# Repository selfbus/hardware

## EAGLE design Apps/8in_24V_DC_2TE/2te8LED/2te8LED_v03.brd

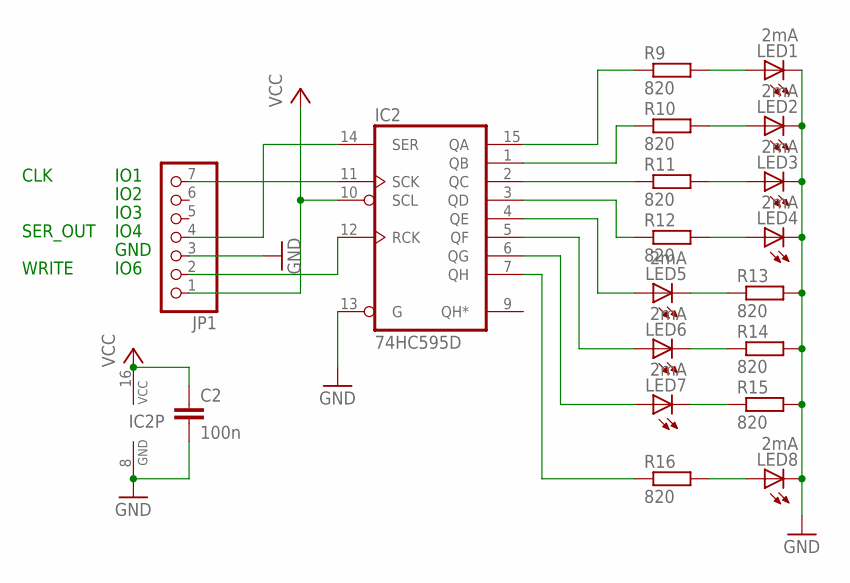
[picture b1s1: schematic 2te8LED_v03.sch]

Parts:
C2: 100n; C050-024X044
IC2: 74HC595D; SO16
JP1: PINHD-1X7_2.54; 1X07
LED1, LED2, LED3, LED4, LED5, LED6, LED7, LED8: 2mA; LED3MM
R9, R10, R11, R12, R13, R14, R15, R16: 820; 0204/7

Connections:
GND: C2.2, IC2.8 (GND), IC2.13 (G), JP1.3, LED1.K (C), LED2.K (C), LED3.K (C), LED4.K (C), LED8.K (C), R13.2, R14.2, R15.2
IO1: IC2.11 (SCK), JP1.7
IO4: IC2.14 (SER), JP1.4
IO6: IC2.12 (RCK), JP1.2
unnamed: IC2.15 (QA), R9.1
unnamed: IC2.1 (QB), R10.1
unnamed: IC2.2 (QC), R11.1
unnamed: IC2.3 (QD), R12.1
unnamed: IC2.4 (QE), LED5.A
unnamed: IC2.5 (QF), LED6.A
unnamed: IC2.6 (QG), LED7.A
unnamed: LED1.A, R9.2
unnamed: LED2.A, R10.2
unnamed: LED3.A, R11.2
unnamed: LED4.A, R12.2
unnamed: LED5.K (C), R13.1
unnamed: LED6.K (C), R14.1
unnamed: LED7.K (C), R15.1
unnamed: IC2.7 (QH), R16.1
unnamed: LED8.A, R16.2
VCC: C2.1, IC2.10 (SCL), IC2.16 (VCC), JP1.1

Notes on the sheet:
IO1
IO2
IO3
IO4
IO6
GND
CLK
SER_OUT
WRITE

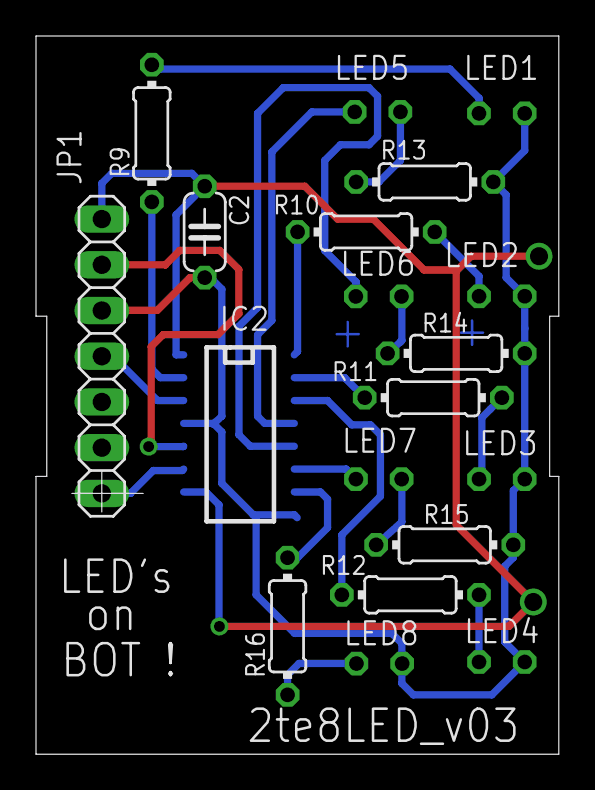
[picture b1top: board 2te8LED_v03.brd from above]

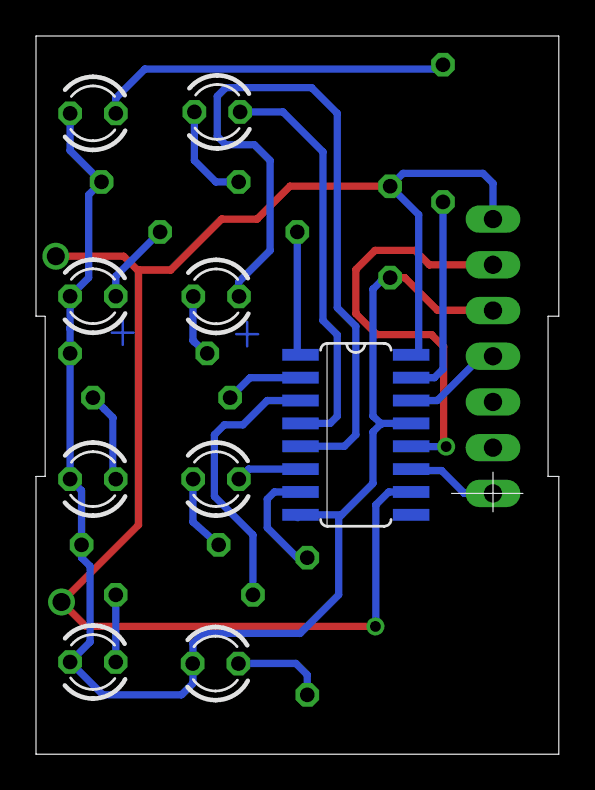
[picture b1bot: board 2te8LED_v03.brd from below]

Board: 2 copper layers, 29.0 x 39.9 mm, 19 parts (9 on the bottom side), 21 nets.
